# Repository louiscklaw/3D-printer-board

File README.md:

### PCB tryout for louis 3d printer
* PCB look like:
	* front:

	* back:

### to initialize the stm32 with klipper firmware
* to flash klipper with stm32duino:
    * `wget 'https://github.com/rogerclarkmelbourne/STM32duino-bootloader/raw/master/binaries/generic_boot20_pc13.bin'`
    * `st-flash /home/logic/_del/7/generic_boot20_pc13.bin 0x8000000`
    * `dfu-util -d 1eaf:0003 -a 2 -R -D out/klipper.bin`

* to flash klipper by st-link
    * `st-flash write klipper.out 0x8000000`

ref: https://github.com/KevinOConnor/klipper/blob/master/docs/Bootloaders.md

### TODO on this REV:
- [x] tidy
- [x] need to confirm about ~~PC13~~ PB9 as debug pin

### Design goal on REV1:
- [x] ~~10~~ 8 channels and ~~10~~ 8 stepper motors
    - [x] x
    - [x] y
    - [x] z0,z1,z2,z3
    - [x] e0,e1,~~e2,e3~~

- [x] ~~5~~ 3 channels PWM control(high power) heaters
    - [x] hotend0, hotend1, ~~hotend2, hotend3~~
    - [x] heatbed

- [x] ~~5~~ 3 channels PWM control(low power) fans
    - [x] hotend0, hotend1, ~~hotend2, hotend3~~
    - [x] heatbed

- [x] 6 and ~~4~~ 1 DI
    - [x] x,y,z min
    - [x] x,y,z max
    - [x] ~~4 misc~~
    - [x] PROBE support

- [x] ~~5~~ 4 + 1  AI(temperature sensors)
    - [x] hotend0,hotend1,~~hotend2,hotend3~~, AUX
    - [x] heatbed
    - [x] PCB temperature self monitoring

### Board source current estimation (**Rough/TBC**):
* stepper motors = 10 * 0.5A ~= 5A
* heatbed = 150W/12 ~= 12A
* hotends = 2 * 20W = 80W ~= 3A

* 12 + 5 + 3 = 20A
* guess taking 0.5 as Diversity factor => 10A

### Thing TODO on next REV(rev/20190518-print1):
- [*] fix inductor footprint (1210)
- [ ] I2C output
- [ ] possibily some digital output channel
- [ ] possibily some SSR channel
- [ ] add debug.sch
- [ ] need to fix and update fan output of stm32
- [ ] 【1808 2410 6125 贴片一次性保险丝管慢断熔断 30A 63V 125V 250V】https://m.tb.cn/h.eW2i21K?sm=9f2ac4 点击链接，再选择浏览器咑閞；或復·制这段描述￥EhubY24cRFh￥后到👉淘♂寳♀👈
- [ ] 4V贴片0805压敏电阻5.6V 14V 17 18 22 25 30 39 40 50 65 68 82V
- [ ] put some 1117 for spare
- [ ] add protector to 5V and 3v3 users
- [ ] add mcu debug led for output
- [ ] stm32 power source controlled by the usb power of orange pi
- [ ] need to take care restart problem
- [ ] stm32 debug usb, add component to get direct access to the stm32 pa11, pa12 as a usb device
- [ ] add varistor to protect stm32 and orange pi
- [ ] avoid using PA0 as
- [ ] add diode to xmin, xmax, ymin, ymax, like zmax and zmin for active sensors
- [ ] dry contact test ok
- [ ] add connected=high to the boot1 and boot0 pin

### Thing TODO on next REV (xxxxxxx):
- [ ] replacement for Orange Pi as too big in size

### Misc:
* pinmapping
    * https://github.com/KevinOConnor/klipper/blob/master/docs/stm32f1.md

* Constrains on STM32:
> When using serial, the UART used for communication with the host is fixed to pins PA9 (TX) and PA10 (RX).
> When using USB, the PA11 (D-) and PA12 (D+) pins are reserved.
> The USB code assumes that PA12 (D+) has a fixed pullup resistor attached to it.

> SWD pins (PA13/PA14) are enabled for debugging and cannot be used for any I/O.
> SPI uses pins PB13/PB14/PB15, but the pins can be used as general I/O if SPI is not used.
> Digital I/O

> All pins that aren't part of the fixed set can be used for digital I/O.
> Pins are referred to by their primary name, e.g. PA1.
> Do not try to use Arduino pin aliases in your configuration.
> See ST's datasheets for more details.
> The STM32Duino wiki has more info on the popular "Blue Pill" board.
> Analog inputs

> All ADC-capable pins can be used as analog inputs with the same naming as digital I/O pins.
> Small packages MCUs (e.g. LFQP48) have 10 channels (PA0-PA7, PB0-PB1), while larger package devices have 16 channels (PA0 PA7, PB0-PB1, PC0-PC5).

> SPI
> SPI uses pin PB13 (SCK), PB14 (MISO) and PB15 (MOSI). The clock speed range is 0.15..18 MHz.  Chip select pins do not have any restrictions.

ref: https://github.com/KevinOConnor/klipper/blob/master/docs/stm32f1.md

### to test indicival pins in stm32
```
./klippy-env/bin/python ./klipper/klippy/console.py /dev/ttyACM0 250000

allocate_oids count=1
config_analog_in oid=0 pin=PA0
finalize_config crc=0
get_config
query_analog_in oid=0 clock={clock} sample_ticks=20000 sample_count=8 rest_ticks=6000000 min_value=12005 max_value=32303 range_check_count=4
```

### logs
20190612:
    - update and check mp1584 circuit
    - resume orange pi symbol
    - fix fans terminals

### Ref:
https://github.com/Creworker/orange-pi

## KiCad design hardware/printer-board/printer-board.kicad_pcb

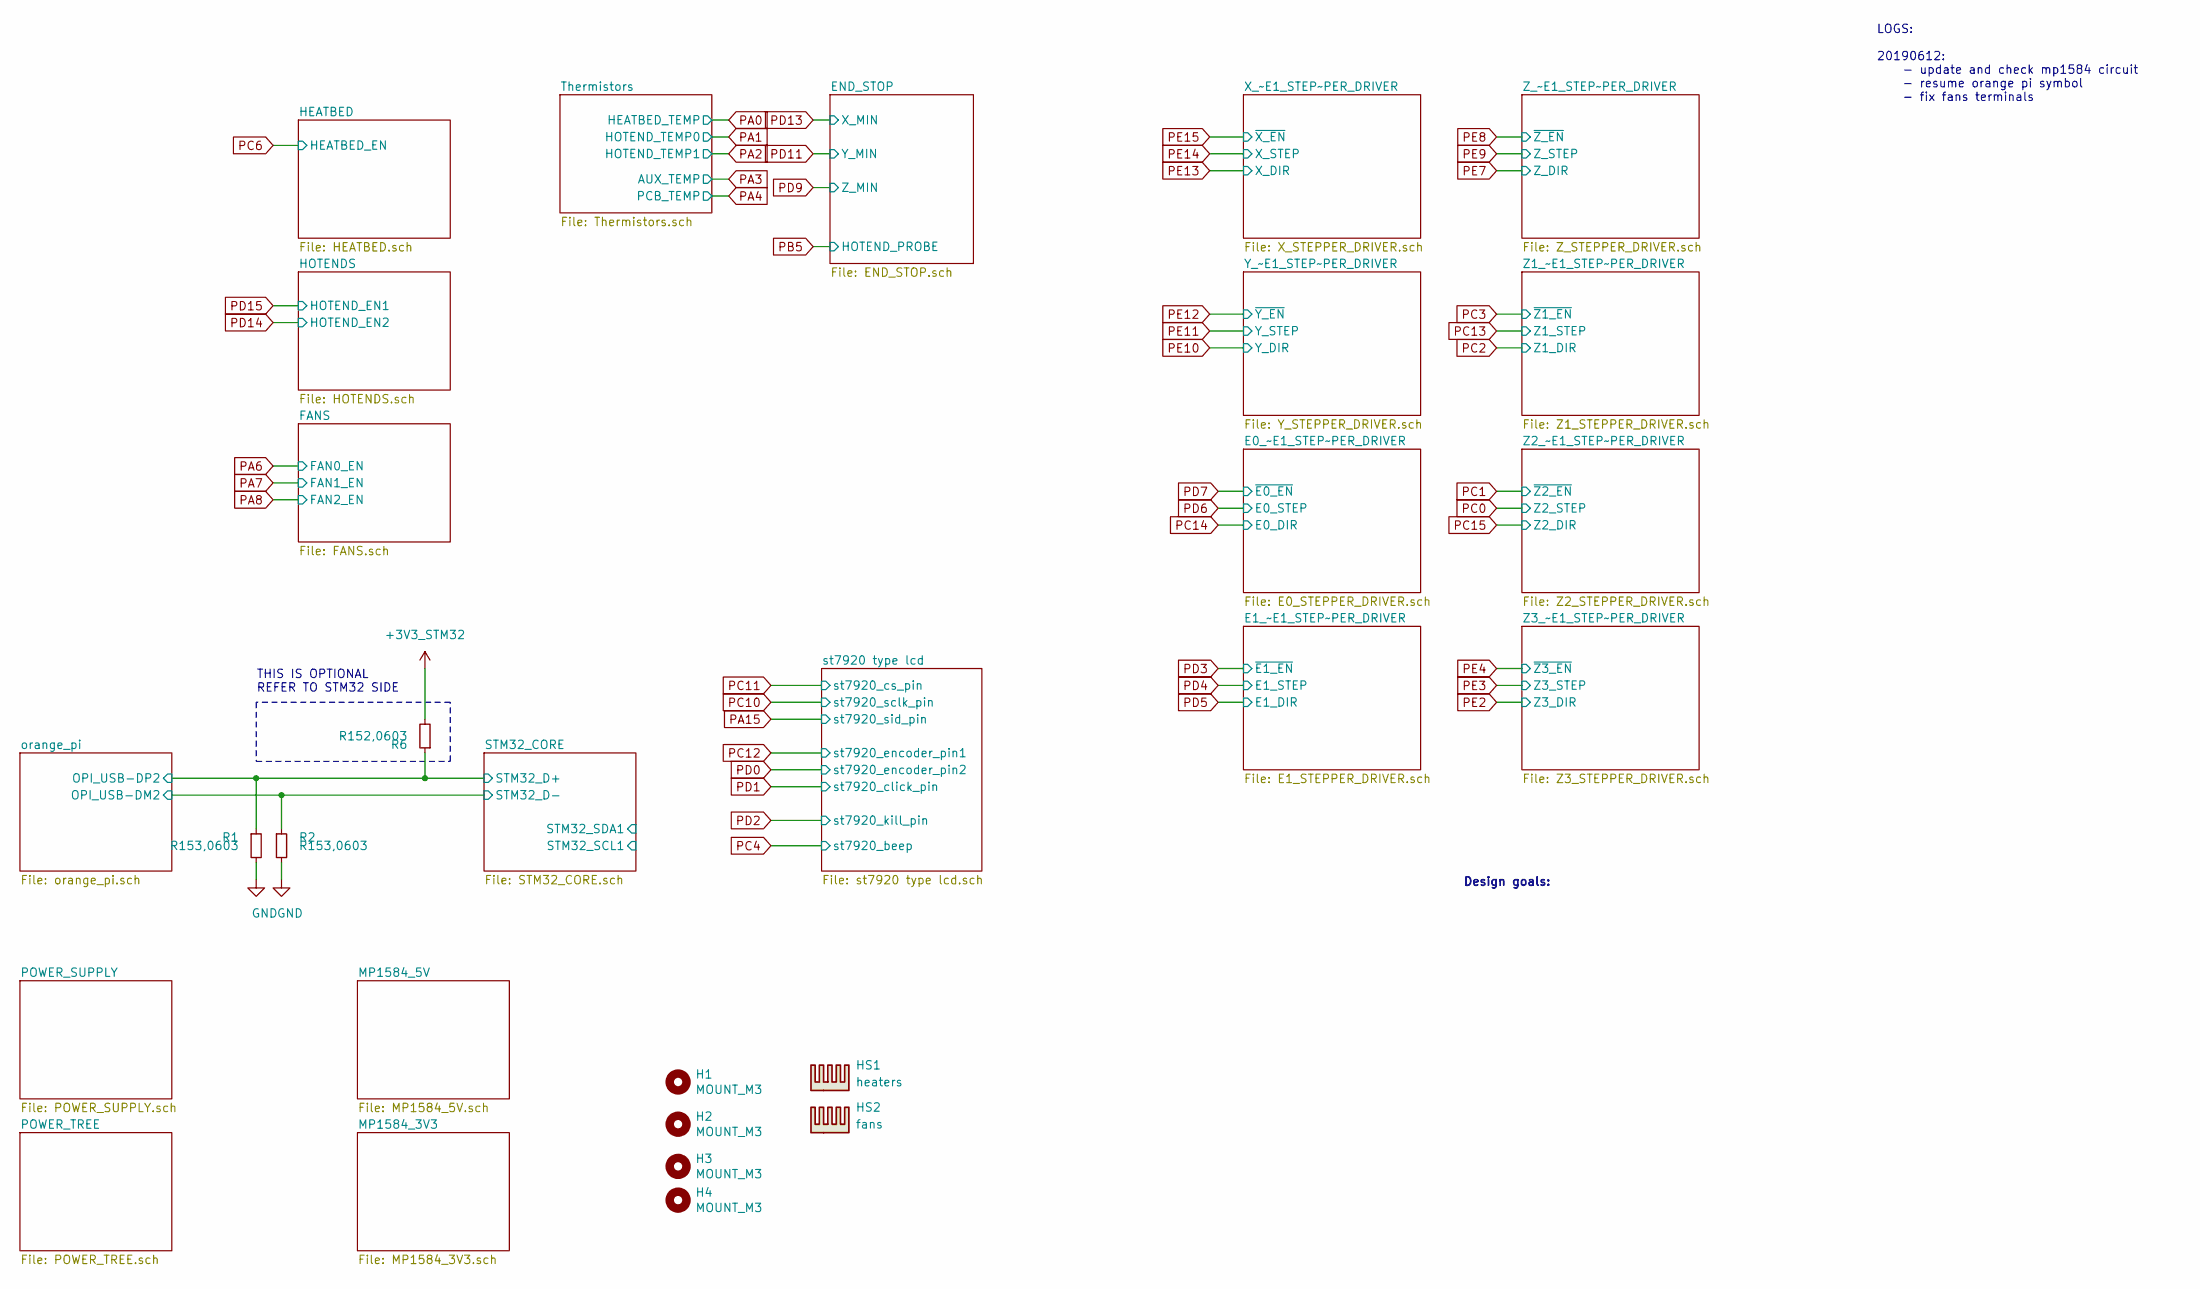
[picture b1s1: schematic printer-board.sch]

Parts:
H1, H2, H3, H4: MOUNT_M3; MountingHole_2.7mm_M2.5,rpi_like
HS1: heaters
HS2: fans
R1, R2: R153,0603; R_0603_1608Metric_Pad1.05x0.95mm_HandSolder
R6: R152,0603; R_0603_1608Metric_Pad1.05x0.95mm_HandSolder

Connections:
/orange_pi/OPI_USB-DM2: R2.1; also elsewhere on the board
/orange_pi/OPI_USB-DP2: R1.1, R6.1; also elsewhere on the board
GND: R1.2, R2.2; also elsewhere on the board

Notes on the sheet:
Design goals:
THIS IS OPTIONAL REFER TO STM32 SIDE
LOGS: 20190612: - update and check mp1584 circuit - resume orange pi symbol - fix fans terminals

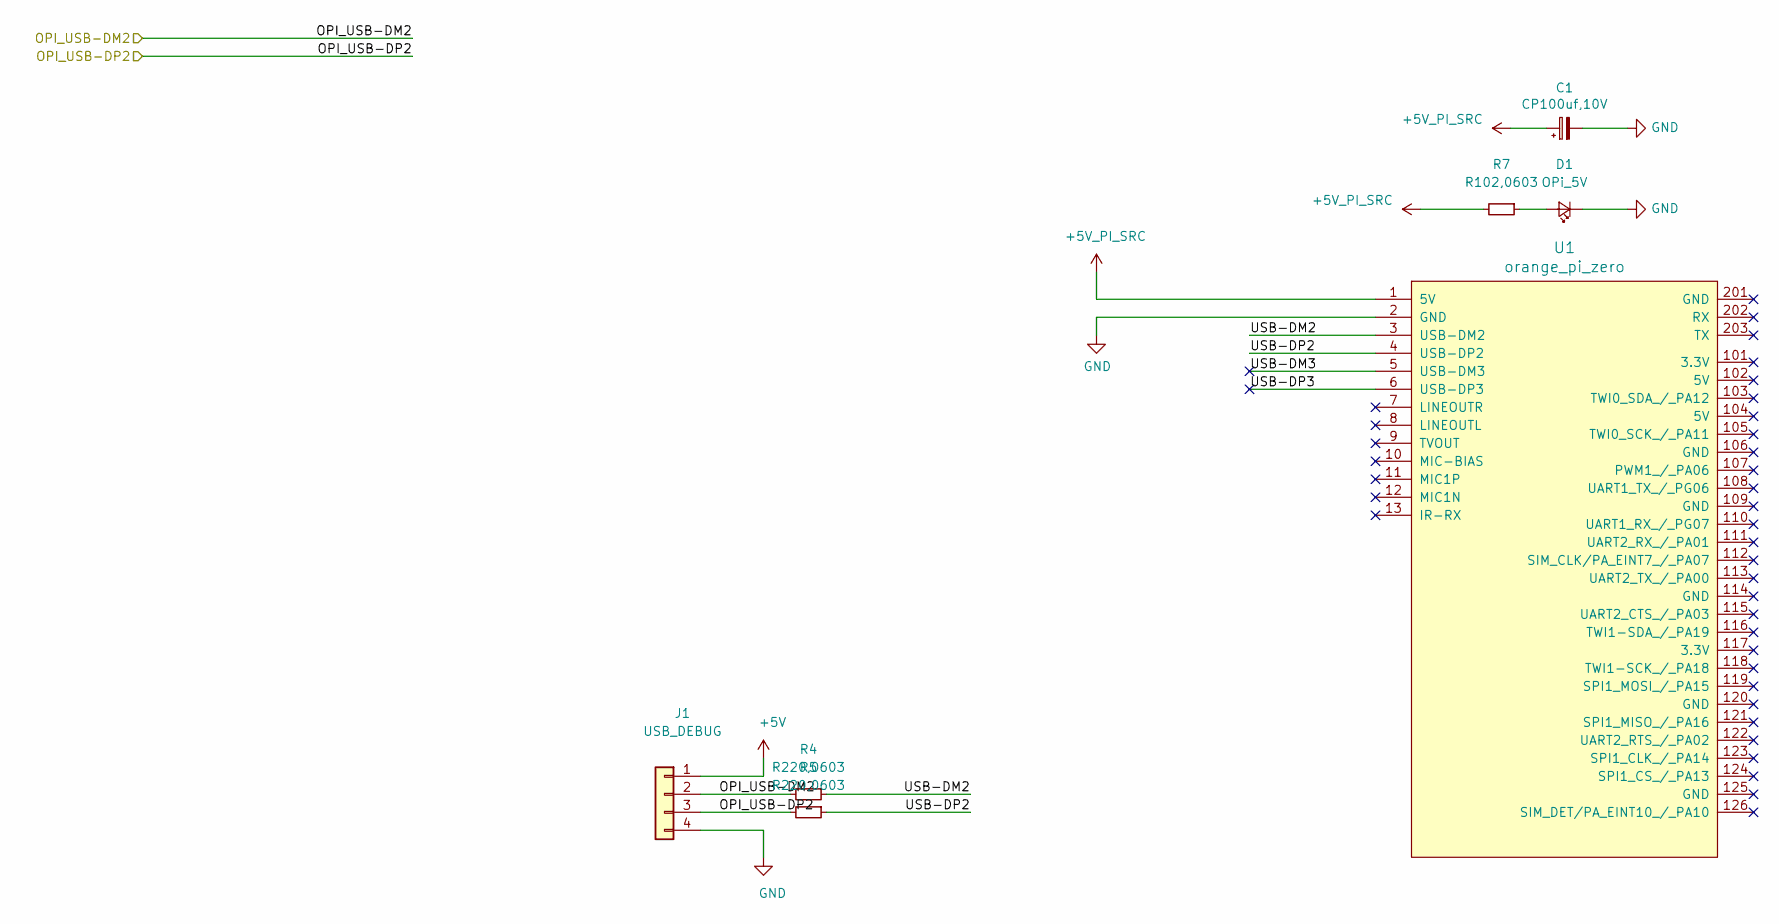
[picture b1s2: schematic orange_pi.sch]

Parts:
C1: CP100uf,10V; CP_Elec_6.3x5.3
D1: OPi_5V; LED_0603_1608Metric_Pad1.05x0.95mm_HandSolder
J1: USB_DEBUG; PinHeader_1x04_P1.27mm_Vertical
R4, R5: R220,0603; R_0603_1608Metric_Pad1.05x0.95mm_HandSolder
R7: R102,0603; R_0603_1608Metric_Pad1.05x0.95mm_HandSolder
U1: orange_pi_zero; orangepi-zero

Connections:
+5V_PI_SRC: C1.1, R7.2, U1.1 (5V); also elsewhere on the board
/orange_pi/OPI_USB-DM2: J1.2, R4.2; also elsewhere on the board
/orange_pi/OPI_USB-DP2: J1.3, R5.2; also elsewhere on the board
/orange_pi/USB-DM2: R4.1, U1.3 (USB-DM2)
/orange_pi/USB-DM3: U1.5 (USB-DM3)
/orange_pi/USB-DP2: R5.1, U1.4 (USB-DP2)
/orange_pi/USB-DP3: U1.6 (USB-DP3)
GND: C1.2, D1.1 (K), J1.4, U1.2 (GND); also elsewhere on the board
unnamed: D1.2 (A), R7.1

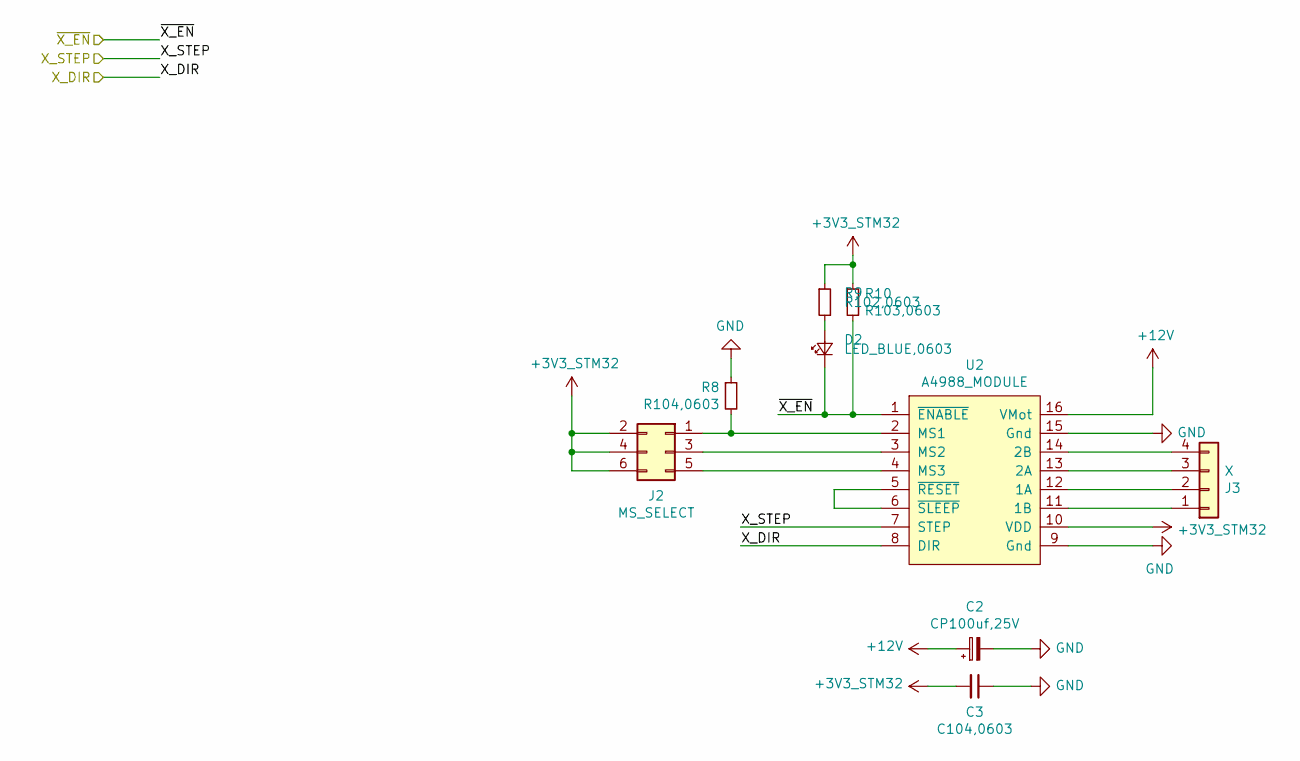
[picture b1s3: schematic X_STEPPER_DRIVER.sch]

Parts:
C2: CP100uf,25V; CP_Elec_6.3x7.7
C3: C104,0603; C_0603_1608Metric_Pad1.05x0.95mm_HandSolder
D2: LED_BLUE,0603; LED_0603_1608Metric_Pad1.05x0.95mm_HandSolder
J2: MS_SELECT; PinHeader_2x03_P2.54mm_Vertical
J3: X; b4b-ph-kl,stepper_terminal
R8: R104,0603; R_0603_1608Metric_Pad1.05x0.95mm_HandSolder
R9: R102,0603; R_0603_1608Metric_Pad1.05x0.95mm_HandSolder
R10: R103,0603; R_0603_1608Metric_Pad1.05x0.95mm_HandSolder
U2: A4988_MODULE; Pololu_Breakout-16_15.2x20.3mm

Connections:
+12V: C2.1, U2.16 (VMot); also elsewhere on the board
GND: C2.2, C3.1, R8.1, U2.9 (Gnd), U2.15 (Gnd); also elsewhere on the board
unnamed: D2.2 (A), R9.2
unnamed: J2.1, R8.2, U2.2 (MS1)
unnamed: J2.3, U2.3 (MS2)
unnamed: J2.5, U2.4 (MS3)
unnamed: J3.1, U2.11 (1B)
unnamed: J3.2, U2.12 (1A)
unnamed: J3.3, U2.13 (2A)
unnamed: J3.4, U2.14 (2B)
unnamed: U2.5 (~RESET~), U2.6 (~SLEEP~)
PE13: U2.8 (DIR); also elsewhere on the board
PE14: U2.7 (STEP); also elsewhere on the board
PE15: D2.1 (K), R10.2, U2.1 (~ENABLE~); also elsewhere on the board

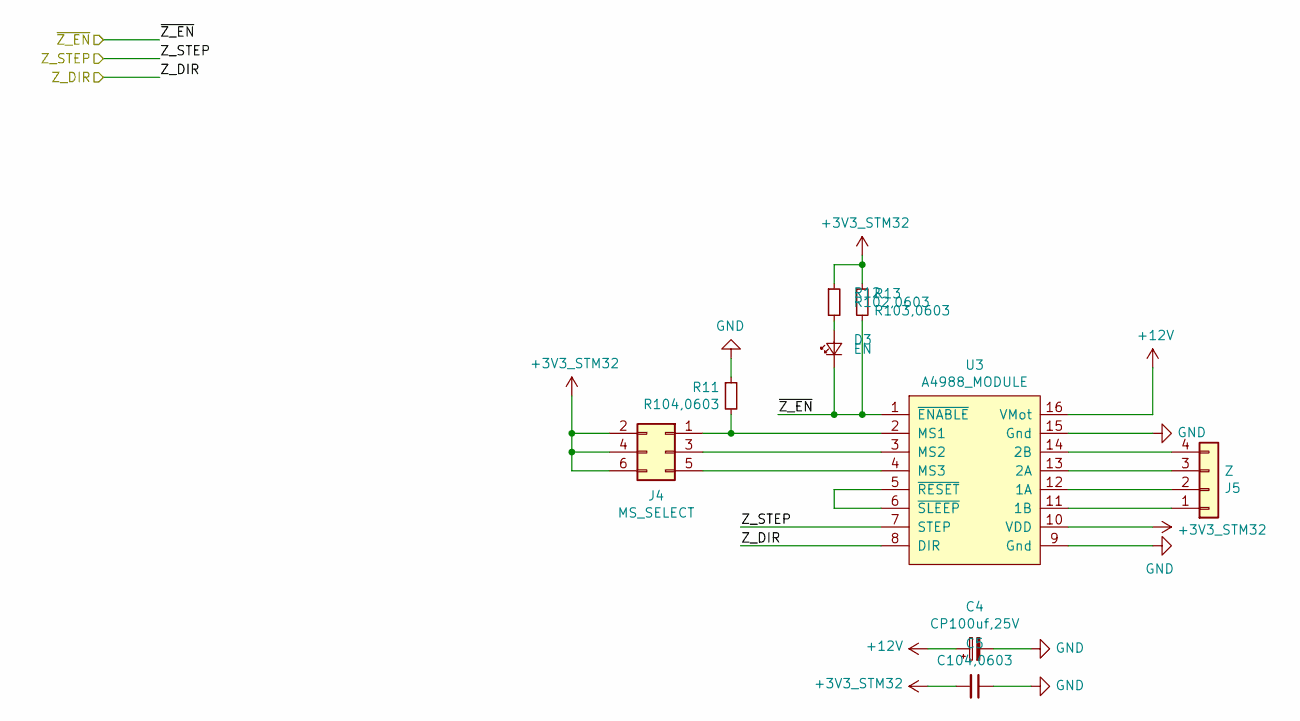
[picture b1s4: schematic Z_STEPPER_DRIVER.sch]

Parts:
C4: CP100uf,25V; CP_Elec_6.3x7.7
C5: C104,0603; C_0603_1608Metric_Pad1.05x0.95mm_HandSolder
D3: EN; LED_0603_1608Metric_Pad1.05x0.95mm_HandSolder
J4: MS_SELECT; PinHeader_2x03_P2.54mm_Vertical
J5: Z; STEP_MOTOR_2.54_TERMINAL
R11: R104,0603; R_0603_1608Metric_Pad1.05x0.95mm_HandSolder
R12: R102,0603; R_0603_1608Metric_Pad1.05x0.95mm_HandSolder
R13: R103,0603; R_0603_1608Metric_Pad1.05x0.95mm_HandSolder
U3: A4988_MODULE; Pololu_Breakout-16_15.2x20.3mm

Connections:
+12V: C4.1, U3.16 (VMot); also elsewhere on the board
GND: C4.2, C5.1, R11.1, U3.9 (Gnd), U3.15 (Gnd); also elsewhere on the board
unnamed: D3.2 (A), R12.2
unnamed: J4.1, R11.2, U3.2 (MS1)
unnamed: J4.3, U3.3 (MS2)
unnamed: J4.5, U3.4 (MS3)
unnamed: J5.1, U3.11 (1B)
unnamed: J5.2, U3.12 (1A)
unnamed: J5.3, U3.13 (2A)
unnamed: J5.4, U3.14 (2B)
unnamed: U3.5 (~RESET~), U3.6 (~SLEEP~)
PE7: U3.8 (DIR); also elsewhere on the board
PE8: D3.1 (K), R13.2, U3.1 (~ENABLE~); also elsewhere on the board
PE9: U3.7 (STEP); also elsewhere on the board

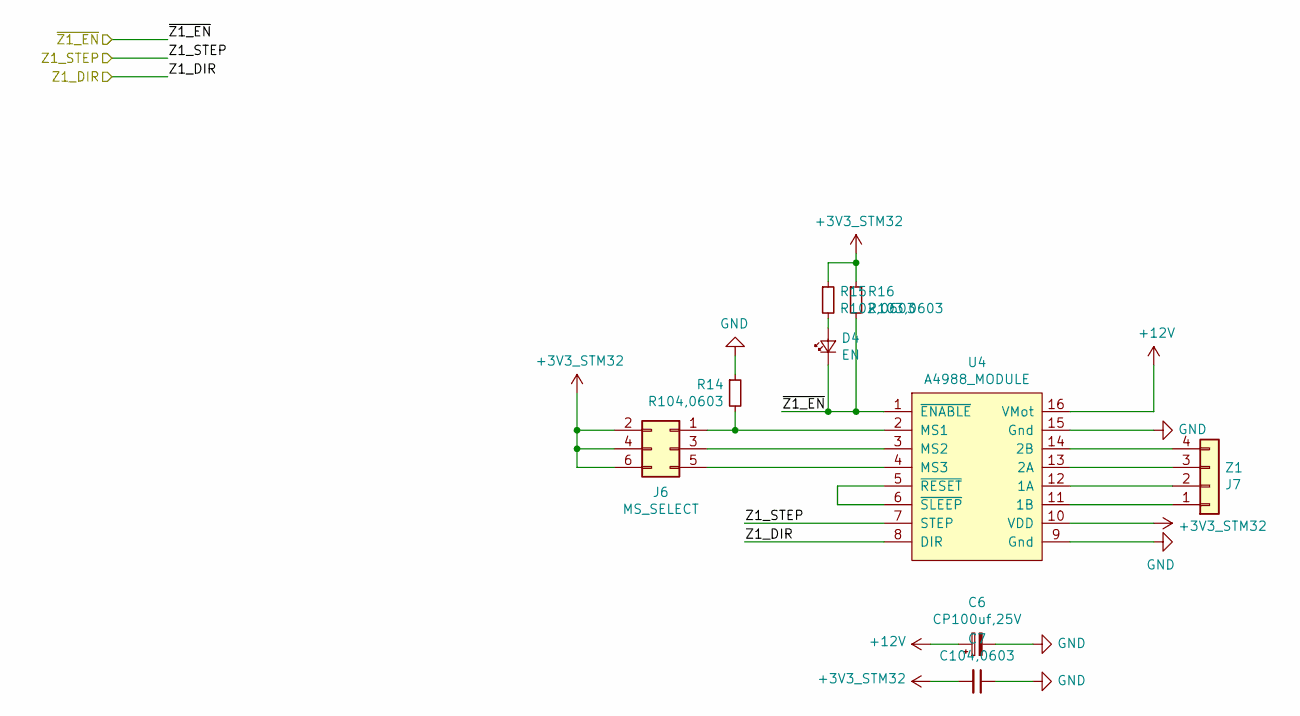
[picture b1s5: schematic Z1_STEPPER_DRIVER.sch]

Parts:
C6: CP100uf,25V; CP_Elec_6.3x7.7
C7: C104,0603; C_0603_1608Metric_Pad1.05x0.95mm_HandSolder
D4: EN; LED_0603_1608Metric_Pad1.05x0.95mm_HandSolder
J6: MS_SELECT; PinHeader_2x03_P2.54mm_Vertical
J7: Z1; STEP_MOTOR_2.54_TERMINAL
R14: R104,0603; R_0603_1608Metric_Pad1.05x0.95mm_HandSolder
R15: R102,0603; R_0603_1608Metric_Pad1.05x0.95mm_HandSolder
R16: R103,0603; R_0603_1608Metric_Pad1.05x0.95mm_HandSolder
U4: A4988_MODULE; Pololu_Breakout-16_15.2x20.3mm

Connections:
+12V: C6.1, U4.16 (VMot); also elsewhere on the board
GND: C6.2, C7.1, R14.1, U4.9 (Gnd), U4.15 (Gnd); also elsewhere on the board
unnamed: D4.2 (A), R15.2
unnamed: J6.1, R14.2, U4.2 (MS1)
unnamed: J6.3, U4.3 (MS2)
unnamed: J6.5, U4.4 (MS3)
unnamed: J7.1, U4.11 (1B)
unnamed: J7.2, U4.12 (1A)
unnamed: J7.3, U4.13 (2A)
unnamed: J7.4, U4.14 (2B)
unnamed: U4.5 (~RESET~), U4.6 (~SLEEP~)
PC2: U4.8 (DIR); also elsewhere on the board
PC3: D4.1 (K), R16.2, U4.1 (~ENABLE~); also elsewhere on the board
PC13: U4.7 (STEP); also elsewhere on the board

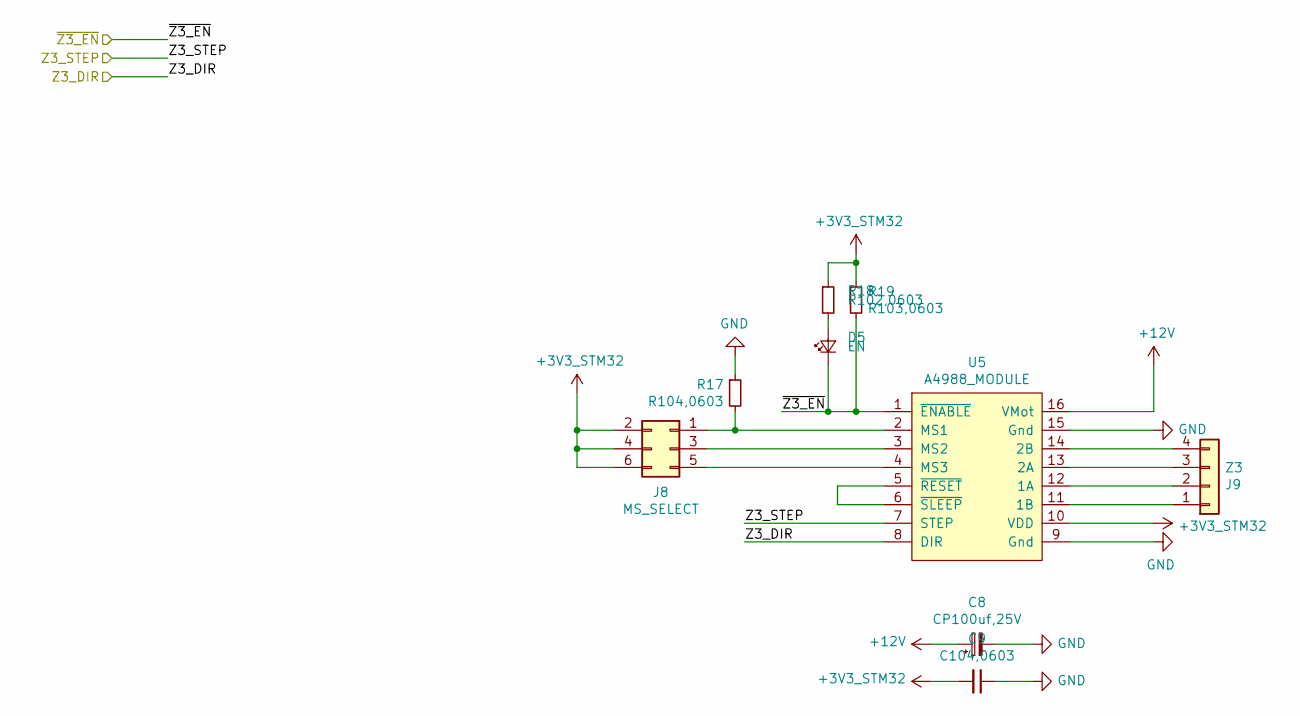
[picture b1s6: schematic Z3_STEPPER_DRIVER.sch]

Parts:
C8: CP100uf,25V; CP_Elec_6.3x7.7
C9: C104,0603; C_0603_1608Metric_Pad1.05x0.95mm_HandSolder
D5: EN; LED_0603_1608Metric_Pad1.05x0.95mm_HandSolder
J8: MS_SELECT; PinHeader_2x03_P2.54mm_Vertical
J9: Z3; STEP_MOTOR_2.54_TERMINAL
R17: R104,0603; R_0603_1608Metric_Pad1.05x0.95mm_HandSolder
R18: R102,0603; R_0603_1608Metric_Pad1.05x0.95mm_HandSolder
R19: R103,0603; R_0603_1608Metric_Pad1.05x0.95mm_HandSolder
U5: A4988_MODULE; Pololu_Breakout-16_15.2x20.3mm

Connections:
+12V: C8.1, U5.16 (VMot); also elsewhere on the board
GND: C8.2, C9.1, R17.1, U5.9 (Gnd), U5.15 (Gnd); also elsewhere on the board
unnamed: D5.2 (A), R18.2
unnamed: J8.1, R17.2, U5.2 (MS1)
unnamed: J8.3, U5.3 (MS2)
unnamed: J8.5, U5.4 (MS3)
unnamed: J9.1, U5.11 (1B)
unnamed: J9.2, U5.12 (1A)
unnamed: J9.3, U5.13 (2A)
unnamed: J9.4, U5.14 (2B)
unnamed: U5.5 (~RESET~), U5.6 (~SLEEP~)
PE2: U5.8 (DIR); also elsewhere on the board
PE3: U5.7 (STEP); also elsewhere on the board
PE4: D5.1 (K), R19.2, U5.1 (~ENABLE~); also elsewhere on the board

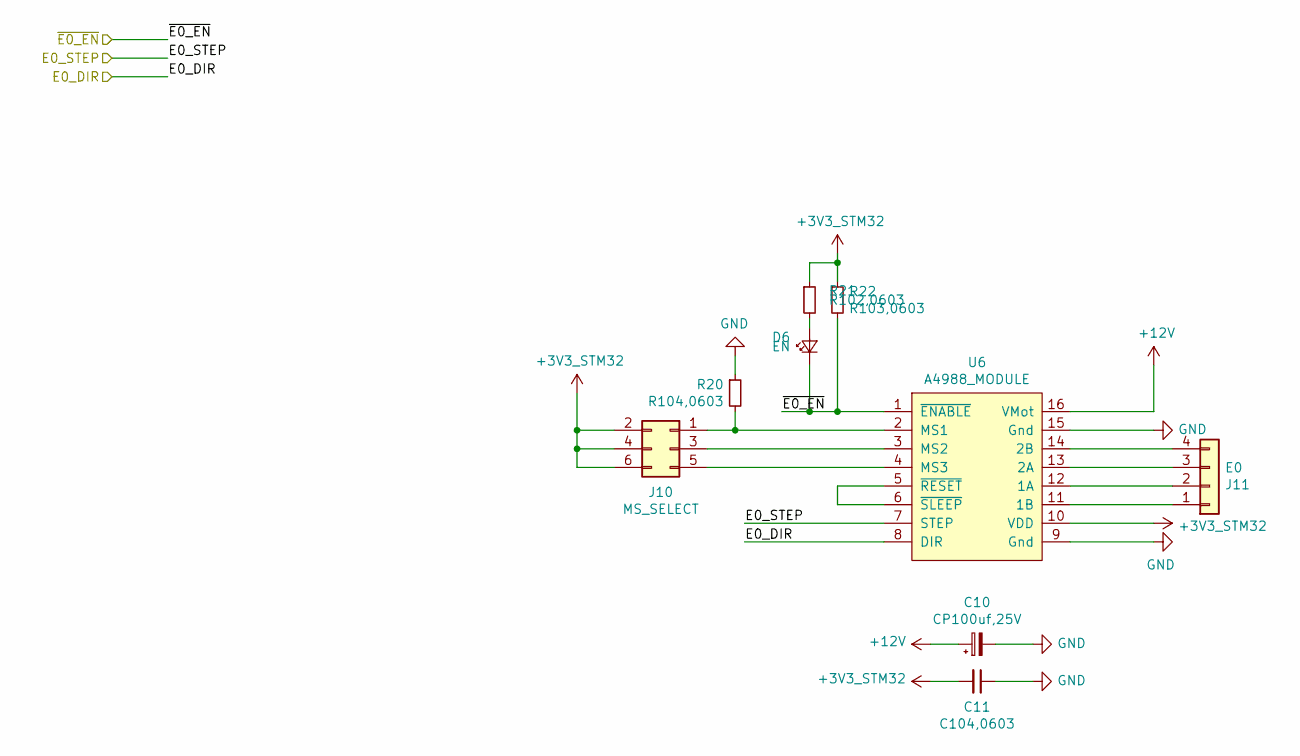
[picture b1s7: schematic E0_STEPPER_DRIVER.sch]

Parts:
C10: CP100uf,25V; CP_Elec_6.3x7.7
C11: C104,0603; C_0603_1608Metric_Pad1.05x0.95mm_HandSolder
D6: EN; LED_0603_1608Metric_Pad1.05x0.95mm_HandSolder
J10: MS_SELECT; PinHeader_2x03_P2.54mm_Vertical
J11: E0; STEP_MOTOR_2.54_TERMINAL
R20: R104,0603; R_0603_1608Metric_Pad1.05x0.95mm_HandSolder
R21: R102,0603; R_0603_1608Metric_Pad1.05x0.95mm_HandSolder
R22: R103,0603; R_0603_1608Metric_Pad1.05x0.95mm_HandSolder
U6: A4988_MODULE; Pololu_Breakout-16_15.2x20.3mm

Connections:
+12V: C10.1, U6.16 (VMot); also elsewhere on the board
GND: C10.2, C11.1, R20.1, U6.9 (Gnd), U6.15 (Gnd); also elsewhere on the board
unnamed: D6.2 (A), R21.2
unnamed: J10.1, R20.2, U6.2 (MS1)
unnamed: J10.3, U6.3 (MS2)
unnamed: J10.5, U6.4 (MS3)
unnamed: J11.1, U6.11 (1B)
unnamed: J11.2, U6.12 (1A)
unnamed: J11.3, U6.13 (2A)
unnamed: J11.4, U6.14 (2B)
unnamed: U6.5 (~RESET~), U6.6 (~SLEEP~)
PC14: U6.8 (DIR); also elsewhere on the board
PD6: U6.7 (STEP); also elsewhere on the board
PD7: D6.1 (K), R22.2, U6.1 (~ENABLE~); also elsewhere on the board

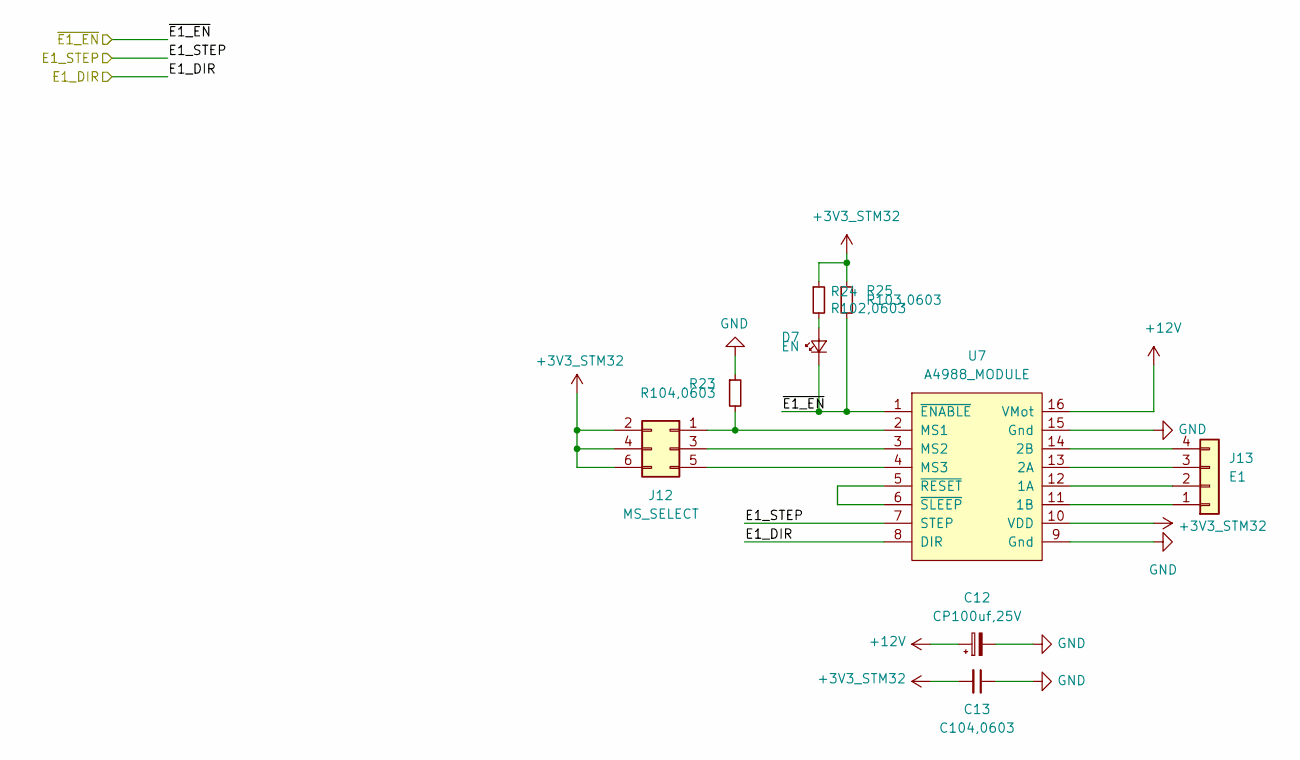
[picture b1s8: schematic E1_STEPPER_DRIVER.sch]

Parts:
C12: CP100uf,25V; CP_Elec_6.3x7.7
C13: C104,0603; C_0603_1608Metric_Pad1.05x0.95mm_HandSolder
D7: EN; LED_0603_1608Metric_Pad1.05x0.95mm_HandSolder
J12: MS_SELECT; PinHeader_2x03_P2.54mm_Vertical
J13: E1; STEP_MOTOR_2.54_TERMINAL
R23: R104,0603; R_0603_1608Metric_Pad1.05x0.95mm_HandSolder
R24: R102,0603; R_0603_1608Metric_Pad1.05x0.95mm_HandSolder
R25: R103,0603; R_0603_1608Metric_Pad1.05x0.95mm_HandSolder
U7: A4988_MODULE; Pololu_Breakout-16_15.2x20.3mm

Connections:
+12V: C12.1, U7.16 (VMot); also elsewhere on the board
GND: C12.2, C13.1, R23.1, U7.9 (Gnd), U7.15 (Gnd); also elsewhere on the board
unnamed: D7.2 (A), R24.2
unnamed: J12.1, R23.2, U7.2 (MS1)
unnamed: J12.3, U7.3 (MS2)
unnamed: J12.5, U7.4 (MS3)
unnamed: J13.1, U7.11 (1B)
unnamed: J13.2, U7.12 (1A)
unnamed: J13.3, U7.13 (2A)
unnamed: J13.4, U7.14 (2B)
unnamed: U7.5 (~RESET~), U7.6 (~SLEEP~)
PD3: D7.1 (K), R25.2, U7.1 (~ENABLE~); also elsewhere on the board
PD4: U7.7 (STEP); also elsewhere on the board
PD5: U7.8 (DIR); also elsewhere on the board

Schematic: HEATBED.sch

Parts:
D8: LED_RED,0603; LED_0603_1608Metric_Pad1.05x0.95mm_HandSolder
J14: HEATBED; mpt_0,5%2f2-2,54,heatbed
Q1: WSK220N04; TO-263-2,thermal_vias
R26: R100,0805; R_0805_2012Metric_Pad1.15x1.40mm_HandSolder
R27: R104,0805; R_0805_2012Metric_Pad1.15x1.40mm_HandSolder
R28: R182,0603; R_0603_1608Metric_Pad1.05x0.95mm_HandSolder

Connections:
+12V2: J14.1, R28.2; also elsewhere on the board
/HEATBED/-12V2: D8.1 (K), J14.2, Q1.2 (D)
GND: Q1.3 (S), R27.1; also elsewhere on the board
unnamed: D8.2 (A), R28.1
unnamed: Q1.1 (G), R26.1
unnamed 150: R26.2, R27.2; also elsewhere on the board

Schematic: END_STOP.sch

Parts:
D9: XMIN; LED_0603_1608Metric_Pad1.05x0.95mm_HandSolder
D10, D11, D12, D13, D14, D15: LED_BLUE,0603; LED_0603_1608Metric_Pad1.05x0.95mm_HandSolder
D16, D25, D26: SD_1N5817_SS12
J15: X_MIN; b3b-ph-kl,end_stop
J16: X_MAX; b3b-ph-kl,end_stop
J17: Y_MIN; b3b-ph-kl,end_stop
J18: Y_MAX; b3b-ph-kl,end_stop
J19: Z_MIN; b3b-ph-kl,end_stop
J20: Z_MAX; b3b-ph-kl,end_stop
J45: END_SWITCH_DEBUG; PinHeader_1x06_P1.27mm_Vertical
J48: HOTEND_PROBE; b3b-ph-kl,end_stop
JP1, JP2: SolderJumper_2_Open
R29, R30, R31, R32, R33, R34, R49: R102,0603; R_0603_1608Metric_Pad1.05x0.95mm_HandSolder

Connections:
+12V: JP1.1 (A), JP2.1 (A); also elsewhere on the board
GND: J15.3, J16.3, J17.3, J18.3, J19.3, J20.3, J48.3; also elsewhere on the board
unnamed: D9.2 (A), R29.2
unnamed: D11.2 (A), R31.2
unnamed: D12.1 (K), J18.1, J45.4
unnamed: D13.1 (K), D25.1 (K), J19.1
unnamed: D13.2 (A), R33.2
unnamed: D14.1 (K), D26.1 (K), J20.1
unnamed: D15.1 (K), D16.1 (K), J48.1
unnamed: D15.2 (A), R49.2
unnamed: D26.2 (A), J45.6
unnamed: J48.2, JP2.2 (B)
unnamed 150: D10.2 (A), R30.2; also elsewhere on the board
unnamed 152: D14.2 (A), R34.2; also elsewhere on the board
PB5: D16.2 (A); also elsewhere on the board
PC6: D12.2 (A), R32.2; also elsewhere on the board
PD13: D9.1 (K), J15.1, J45.1; also elsewhere on the board

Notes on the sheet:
COM ? SENSOR NO ? POWER NC ? GND
assume dry contact here
protection against active sensor

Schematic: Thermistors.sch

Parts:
C14, C15, C16, C17, C18: C106,0603; C_0603_1608Metric_Pad1.05x0.95mm_HandSolder
J21: HEATBED_T; XH_TEMPERATURE_SENSOR_TERMINAL_2.54
J22: HOTEND_T0; XH_TEMPERATURE_SENSOR_TERMINAL_2.54
J23: HOTEND_T1; XH_TEMPERATURE_SENSOR_TERMINAL_2.54
J24: AUX_T; XH_TEMPERATURE_SENSOR_TERMINAL_2.54
J47: TEMP_DEBUG; PinHeader_1x05_P1.27mm_Vertical
R35, R36, R37, R38, R39: R472,0603; R_0603_1608Metric_Pad1.05x0.95mm_HandSolder
TH1: Thermistor_NTC; R_0603_1608Metric_Pad1.05x0.95mm_HandSolder

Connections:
GND: C14.2, C15.2, C16.2, C17.2, C18.2, J21.2, J22.2, J23.2, J24.2, TH1.2; also elsewhere on the board
PA0: C14.1, J21.1, J47.2, R35.2; also elsewhere on the board
PA1: C15.1, J22.1, J47.3, R36.2; also elsewhere on the board
PA2: C16.1, J23.1, J47.4, R37.2; also elsewhere on the board
PA3: C17.1, J24.1, J47.5, R38.2; also elsewhere on the board
PA4: C18.1, J47.1, R39.2, TH1.1; also elsewhere on the board

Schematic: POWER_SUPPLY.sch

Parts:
C19: C104,0603; C_0603_1608Metric_Pad1.05x0.95mm_HandSolder
C20: CP100uf,25V; CP_Elec_6.3x7.7
F1, F2: 15A; Fuse_holder_SMF_with_via
J25: 12V_IN2; DG_KF128-2
J26: 12V_IN; DG_KF128-2
JP5: 12V_JUMPER; SolderJumper-2_P1.3mm_Open_TrianglePad1.0x1.5mm

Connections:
+12V: C19.1, C20.1, F2.2; also elsewhere on the board
+12V2: F1.2; also elsewhere on the board
/POWER_SUPPLY/12V_IN2_1: F1.1, J25.1, JP5.1
/POWER_SUPPLY/12V_IN_1: F2.1, J26.1, JP5.2
GND: C19.2, C20.2, J25.2, J26.2; also elsewhere on the board

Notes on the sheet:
optional to get another source for +12v2

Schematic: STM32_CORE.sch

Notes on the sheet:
STM32F407VET6(F103VET6/F103VCT6)
When using serial, the UART used for communication with the host is fixed to pins PA9 (TX) and PA10 (RX).

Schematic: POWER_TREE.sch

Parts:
JP8: 5V_PI_EN; SolderJumper-2_P1.3mm_Open_RoundedPad1.0x1.5mm
JP9: 3V_EN; SolderJumper-2_P1.3mm_Open_RoundedPad1.0x1.5mm
TP2: TP_GND; TestPoint_Pad_1.0x1.0mm
TP3: TP_3V3; TestPoint_Pad_1.0x1.0mm
TP4: TP_5V; TestPoint_Pad_1.0x1.0mm
TP5: TP_12V; TestPoint_Pad_1.0x1.0mm

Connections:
+5V_PI_SRC: JP8.2 (B); also elsewhere on the board

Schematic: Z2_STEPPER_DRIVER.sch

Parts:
C39: CP100uf,25V; CP_Elec_6.3x7.7
C40: C104,0603; C_0603_1608Metric_Pad1.05x0.95mm_HandSolder
D23: EN; LED_0603_1608Metric_Pad1.05x0.95mm_HandSolder
J36: MS_SELECT; PinHeader_2x03_P2.54mm_Vertical
J37: Z2; STEP_MOTOR_2.54_TERMINAL
R68: R104,0603; R_0603_1608Metric_Pad1.05x0.95mm_HandSolder
R69: R102,0603; R_0603_1608Metric_Pad1.05x0.95mm_HandSolder
R70: R103,0603; R_0603_1608Metric_Pad1.05x0.95mm_HandSolder
U9: A4988_MODULE; Pololu_Breakout-16_15.2x20.3mm

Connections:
+12V: C39.1, U9.16 (VMot); also elsewhere on the board
GND: C39.2, C40.1, R68.1, U9.9 (Gnd), U9.15 (Gnd); also elsewhere on the board
unnamed: D23.2 (A), R69.2
unnamed: J36.1, R68.2, U9.2 (MS1)
unnamed: J36.3, U9.3 (MS2)
unnamed: J36.5, U9.4 (MS3)
unnamed: J37.1, U9.11 (1B)
unnamed: J37.2, U9.12 (1A)
unnamed: J37.3, U9.13 (2A)
unnamed: J37.4, U9.14 (2B)
unnamed: U9.5 (~RESET~), U9.6 (~SLEEP~)
PC0: U9.7 (STEP); also elsewhere on the board
PC1: D23.1 (K), R70.2, U9.1 (~ENABLE~); also elsewhere on the board
PC15: U9.8 (DIR); also elsewhere on the board

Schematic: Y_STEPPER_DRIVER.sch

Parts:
C41: CP100uf,25V; CP_Elec_6.3x7.7
C42: C104,0603; C_0603_1608Metric_Pad1.05x0.95mm_HandSolder
D24: EN; LED_0603_1608Metric_Pad1.05x0.95mm_HandSolder
J38: MS_SELECT; PinHeader_2x03_P2.54mm_Vertical
J39: Y; STEP_MOTOR_2.54_TERMINAL
R71: R104,0603; R_0603_1608Metric_Pad1.05x0.95mm_HandSolder
R72: R102,0603; R_0603_1608Metric_Pad1.05x0.95mm_HandSolder
R73: R103,0603; R_0603_1608Metric_Pad1.05x0.95mm_HandSolder
U10: A4988_MODULE; Pololu_Breakout-16_15.2x20.3mm

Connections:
+12V: C41.1, U10.16 (VMot); also elsewhere on the board
GND: C41.2, C42.1, R71.1, U10.9 (Gnd), U10.15 (Gnd); also elsewhere on the board
unnamed: D24.2 (A), R72.2
unnamed: J38.1, R71.2, U10.2 (MS1)
unnamed: J38.3, U10.3 (MS2)
unnamed: J38.5, U10.4 (MS3)
unnamed: J39.1, U10.11 (1B)
unnamed: J39.2, U10.12 (1A)
unnamed: J39.3, U10.13 (2A)
unnamed: J39.4, U10.14 (2B)
unnamed: U10.5 (~RESET~), U10.6 (~SLEEP~)
PE10: U10.8 (DIR); also elsewhere on the board
PE11: U10.7 (STEP); also elsewhere on the board
PE12: D24.1 (K), R73.2, U10.1 (~ENABLE~); also elsewhere on the board

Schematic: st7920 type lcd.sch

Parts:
C44: CP100uf,16V; CP_Elec_6.3x5.3
J41: EXP1; PinHeader_2x05_P2.54mm_Vertical
J42: EXP2; PinHeader_2x05_P2.54mm_Vertical

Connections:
/st7920 type lcd/RESET: J42.8
GND: C44.2, J41.9, J42.9; also elsewhere on the board
PA15: J41.3; also elsewhere on the board
PC4: J41.1; also elsewhere on the board
PC10: J41.5; also elsewhere on the board
PC11: J41.4; also elsewhere on the board
PC12: J42.5; also elsewhere on the board
PD0: J42.3; also elsewhere on the board
PD1: J41.2; also elsewhere on the board
PD2: J42.10; also elsewhere on the board

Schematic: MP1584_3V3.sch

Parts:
C34: C104,0603; C_0603_1608Metric_Pad1.05x0.95mm_HandSolder
C35, C56, C57: C106,0805; C_0805_2012Metric_Pad1.15x1.40mm_HandSolder
C43: C151,0603; C_0603_1608Metric_Pad1.05x0.95mm_HandSolder
D27: SD_1N5822_SS34; do214aa
J49: Conn_01x03_Female; PinHeader_1x03_P1.27mm_Vertical
L4: L_15uH; inductor_smd_6.8x3.8mm
R80, R83, R85: R104,0603; R_0603_1608Metric_Pad1.05x0.95mm_HandSolder
R81: R224,0603; R_0603_1608Metric_Pad1.05x0.95mm_HandSolder
R82: R240,0603; R_0603_1608Metric_Pad1.05x0.95mm_HandSolder
R84: R433,0603; R_0603_1608Metric_Pad1.05x0.95mm_HandSolder
U13: MP1584; MP1584,SOIC-8_3.9x4.9mm_P1.27mm,thermal_via

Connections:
+12V: C35.1, J49.2, R80.1, U13.7 (VIN); also elsewhere on the board
GND: C35.2, C56.2, C57.2, D27.2 (A), J49.1, R82.2, R83.2, R84.2, R85.2, U13.5 (GND), U13.G (THERMAL_VIA); also elsewhere on the board
unnamed: C34.1, D27.1 (K), L4.1, U13.1 (SW)
unnamed: C34.2, U13.8 (BST)
unnamed: C43.1, U13.3 (COMP)
unnamed: C43.2, R85.1
unnamed: R80.2, R82.1, U13.2 (EN)
unnamed: R81.2, R84.1, U13.4 (FB)
unnamed: R83.1, U13.6 (FREQ)

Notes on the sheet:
//fixme: need to fix value R81 and R84

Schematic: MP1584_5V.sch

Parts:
C34: C104,0603; C_0603_1608Metric_Pad1.05x0.95mm_HandSolder
C35, C56, C57: C106,0805; C_0805_2012Metric_Pad1.15x1.40mm_HandSolder
C43: C151,0603; C_0603_1608Metric_Pad1.05x0.95mm_HandSolder
D27: SD_1N5822_SS34; do214aa
J49: Conn_01x03_Female; PinHeader_1x03_P1.27mm_Vertical
L4: L_15uH; inductor_smd_6.8x3.8mm
R80, R83, R85: R104,0603; R_0603_1608Metric_Pad1.05x0.95mm_HandSolder
R81: R224,0603; R_0603_1608Metric_Pad1.05x0.95mm_HandSolder
R82: R240,0603; R_0603_1608Metric_Pad1.05x0.95mm_HandSolder
R84: R433,0603; R_0603_1608Metric_Pad1.05x0.95mm_HandSolder
U13: MP1584; MP1584,SOIC-8_3.9x4.9mm_P1.27mm,thermal_via

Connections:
+12V: C35.1, J49.2, R80.1, U13.7 (VIN); also elsewhere on the board
GND: C35.2, C56.2, C57.2, D27.2 (A), J49.1, R82.2, R83.2, R84.2, R85.2, U13.5 (GND), U13.G (THERMAL_VIA); also elsewhere on the board
unnamed: C34.1, D27.1 (K), L4.1, U13.1 (SW)
unnamed: C34.2, U13.8 (BST)
unnamed: C43.1, U13.3 (COMP)
unnamed: C43.2, R85.1
unnamed: R80.2, R82.1, U13.2 (EN)
unnamed: R81.2, R84.1, U13.4 (FB)
unnamed: R83.1, U13.6 (FREQ)
